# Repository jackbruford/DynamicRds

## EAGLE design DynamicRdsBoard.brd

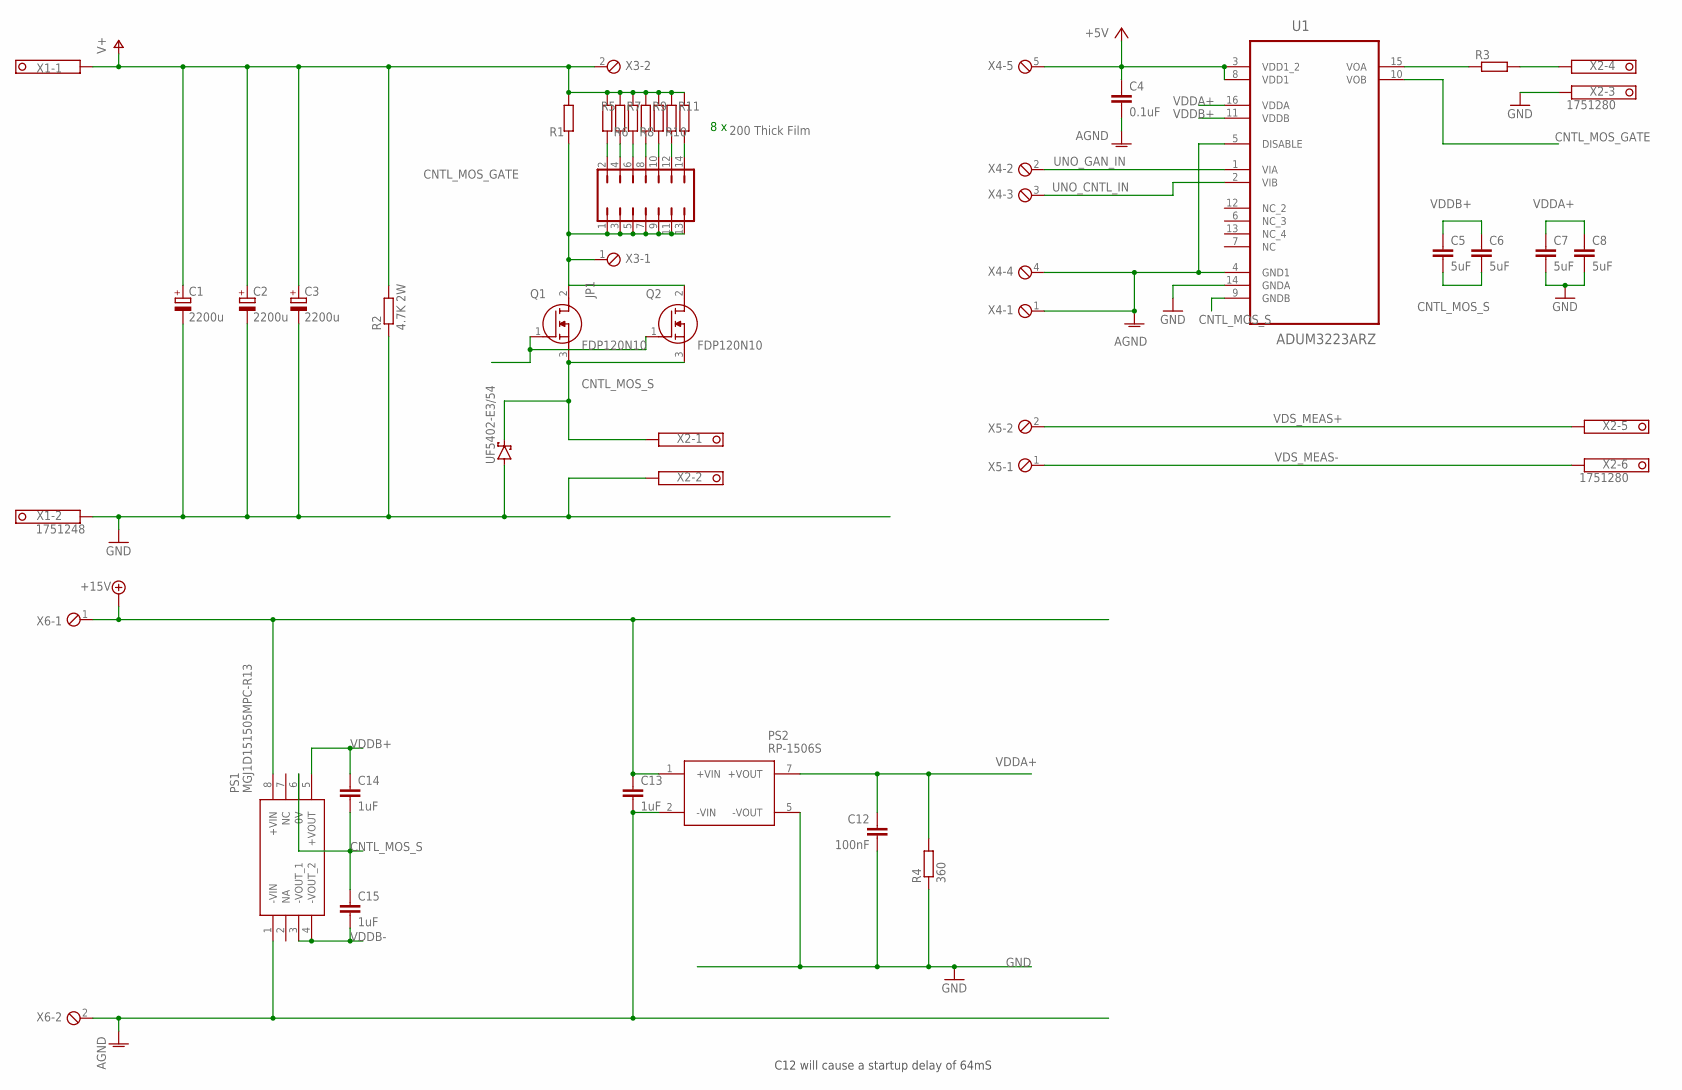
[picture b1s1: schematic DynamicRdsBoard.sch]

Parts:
C1, C2, C3: 2200u; EB30D
C4: 0.1uF; C0805
C5, C6, C7, C8: 5uF; C0805
C12: 100nF; C0805
C13, C14, C15: 1uF; C0805
JP1: JP7Q
PS1: MGJ1D151505MPC-R13; MGJ1D151505MPCR13
PS2: RP-1506S; RP1506S
Q1, Q2: FDP120N10; TO254P483X1016X2261-3P
R1, R5, R6, R7, R8, R9, R10, R11: 200 Thick Film; R1206
R2: 4.7K 2W; 0309/12
R3: R-EU_R0805; R0805
R4: 360; R0805
U1: ADUM3223ARZ; SOIC127P600X175-16N
UF5402-E3/54: SCHOTTKY-DIODECB429-15; CB429-15
X1: 1751248
X2: 1751280
X3, X5, X6: MPT2; 2POL254
X4: MPT5; 5POL254

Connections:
': R3.1, U1.15 (VOA)
+5V: C4.1, U1.3 (VDD1_2), U1.8 (VDD1), X4.5
+15V: C13.1, PS1.8 (+VIN), PS2.1 (+VIN), X6.1
AGND: C4.2, C13.2, PS1.1 (-VIN), PS2.2 (-VIN), U1.4 (GND1), U1.5 (DISABLE), X4.1, X4.4, X6.2
CNTL_MOS_GATE: Q1.1 (G), Q2.1 (G), U1.10 (VOB)
CNTL_MOS_S: C5.2, C6.2, C14.2, C15.1, PS1.6 (0V), Q1.3 (S), Q2.3 (S), U1.9 (GNDB), UF5402-E3/54.C, X2.1
GAN_MOS_G: R3.2, X2.4
GND: C1.-, C2.-, C3.-, C7.2, C8.2, C12.2, PS2.5 (-VOUT), R2.1, R4.1, U1.14 (GNDA), UF5402-E3/54.A, X1.2, X2.2, X2.3
unnamed: JP1.1, JP1.3, JP1.5, JP1.7, JP1.9, JP1.11, JP1.13, Q1.2 (D), Q2.2 (D), R1.1, X3.1
unnamed: JP1.2, R5.1
unnamed: JP1.4, R6.1
unnamed: JP1.6, R7.1
unnamed: JP1.8, R8.1
unnamed: JP1.10, R9.1
unnamed: JP1.12, R10.1
unnamed: JP1.14, R11.1
UNO_CNTL_IN: U1.2 (VIB), X4.3
UNO_GAN_IN: U1.1 (VIA), X4.2
V+: C1.+, C2.+, C3.+, R1.2, R2.2, R5.2, R6.2, R7.2, R8.2, R9.2, R10.2, R11.2, X1.1, X3.2
VDDA+: C7.1, C8.1, C12.1, PS2.7 (+VOUT), R4.2, U1.16 (VDDA)
VDDB+: C5.1, C6.1, C14.1, PS1.5 (+VOUT), U1.11 (VDDB)
VDDB-: C15.2, PS1.3 (-VOUT_1), PS1.4 (-VOUT_2)
VDS_MEAS+: X2.5, X5.2
VDS_MEAS-: X2.6, X5.1

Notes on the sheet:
C12 will cause a startup delay of 64mS
8 x

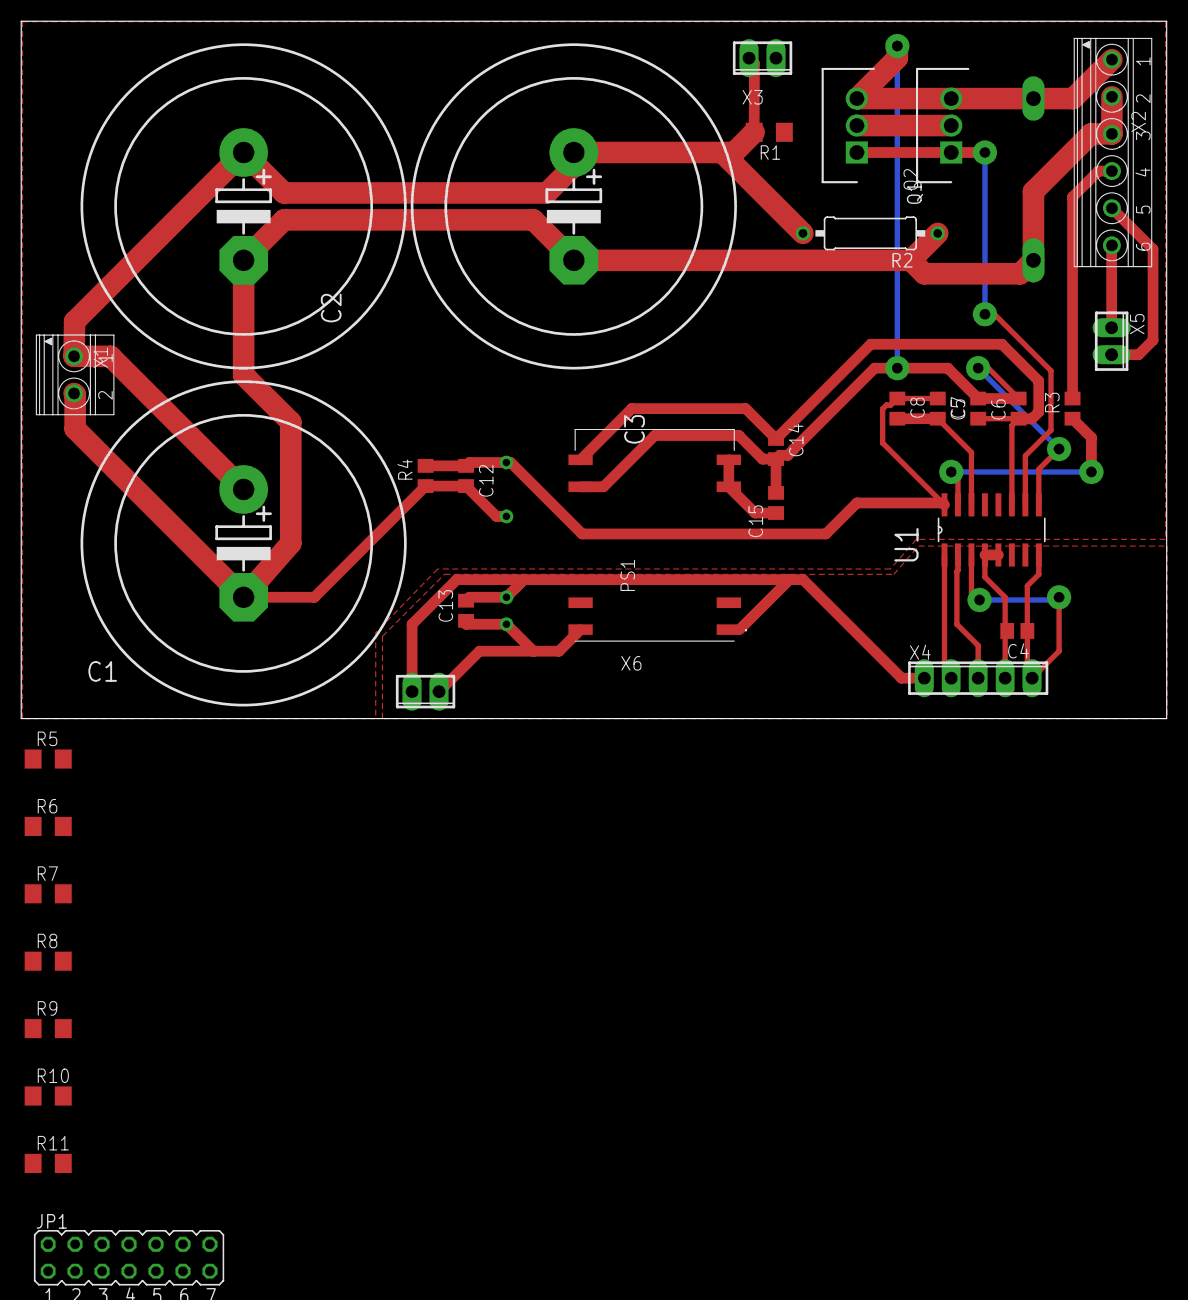
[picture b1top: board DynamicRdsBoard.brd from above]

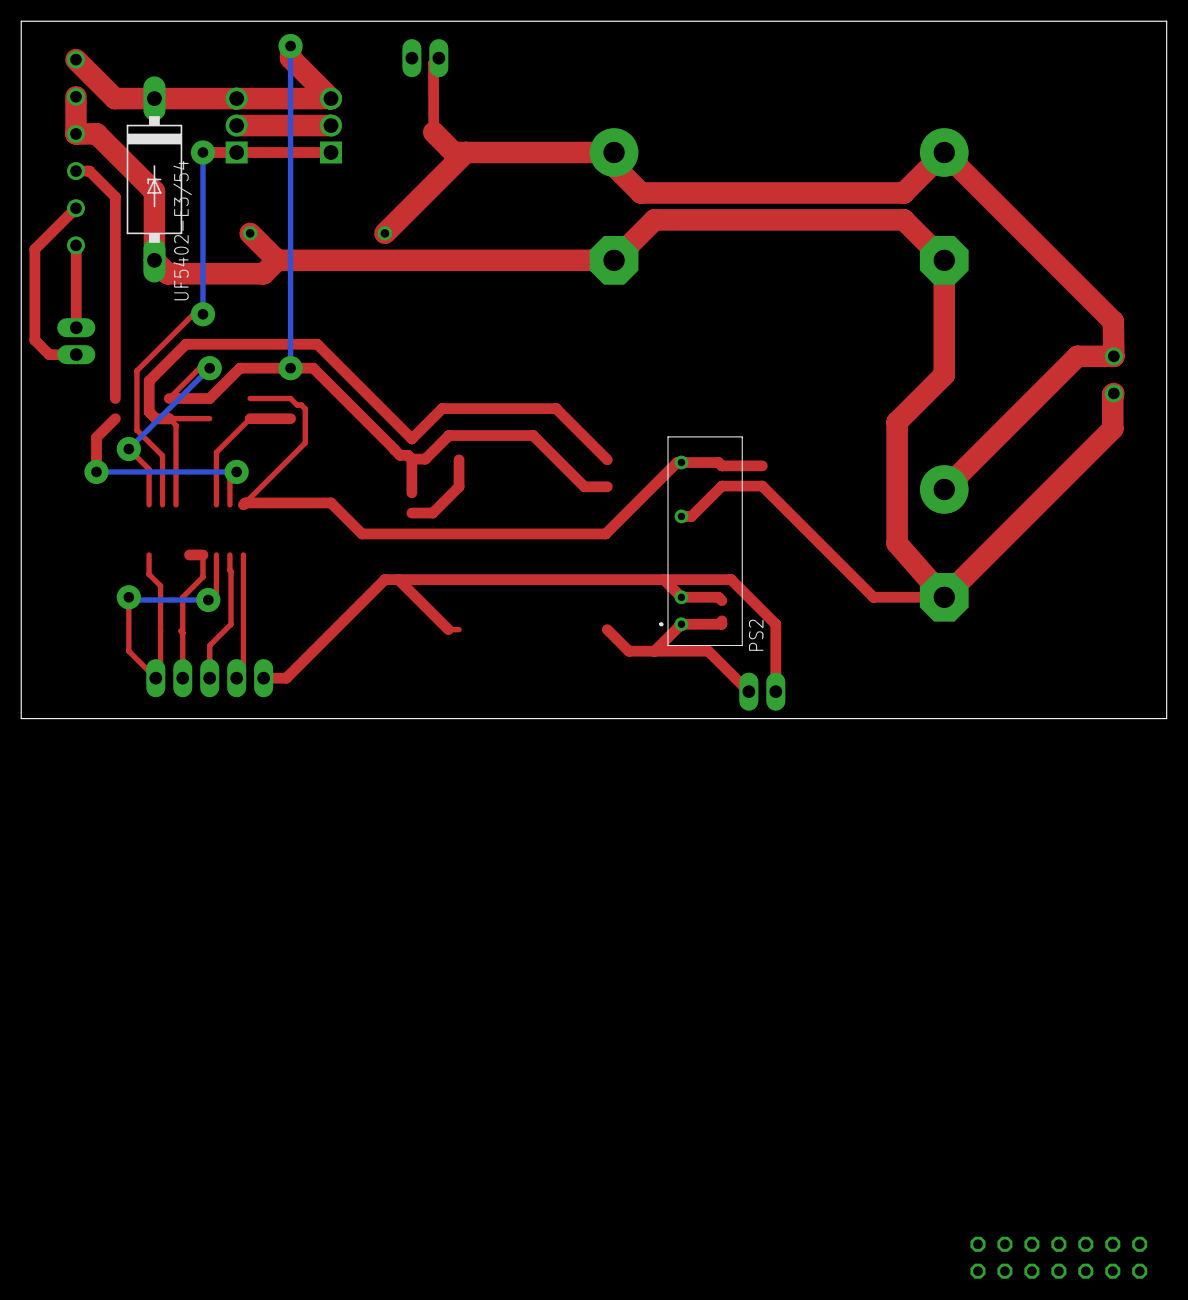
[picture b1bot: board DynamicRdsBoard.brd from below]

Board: 2 copper layers, 107.9 x 65.7 mm, 36 parts (2 on the bottom side), 24 nets.

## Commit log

2021-06-02 Added files from Pulse Test
2021-06-07 Friday work commit
